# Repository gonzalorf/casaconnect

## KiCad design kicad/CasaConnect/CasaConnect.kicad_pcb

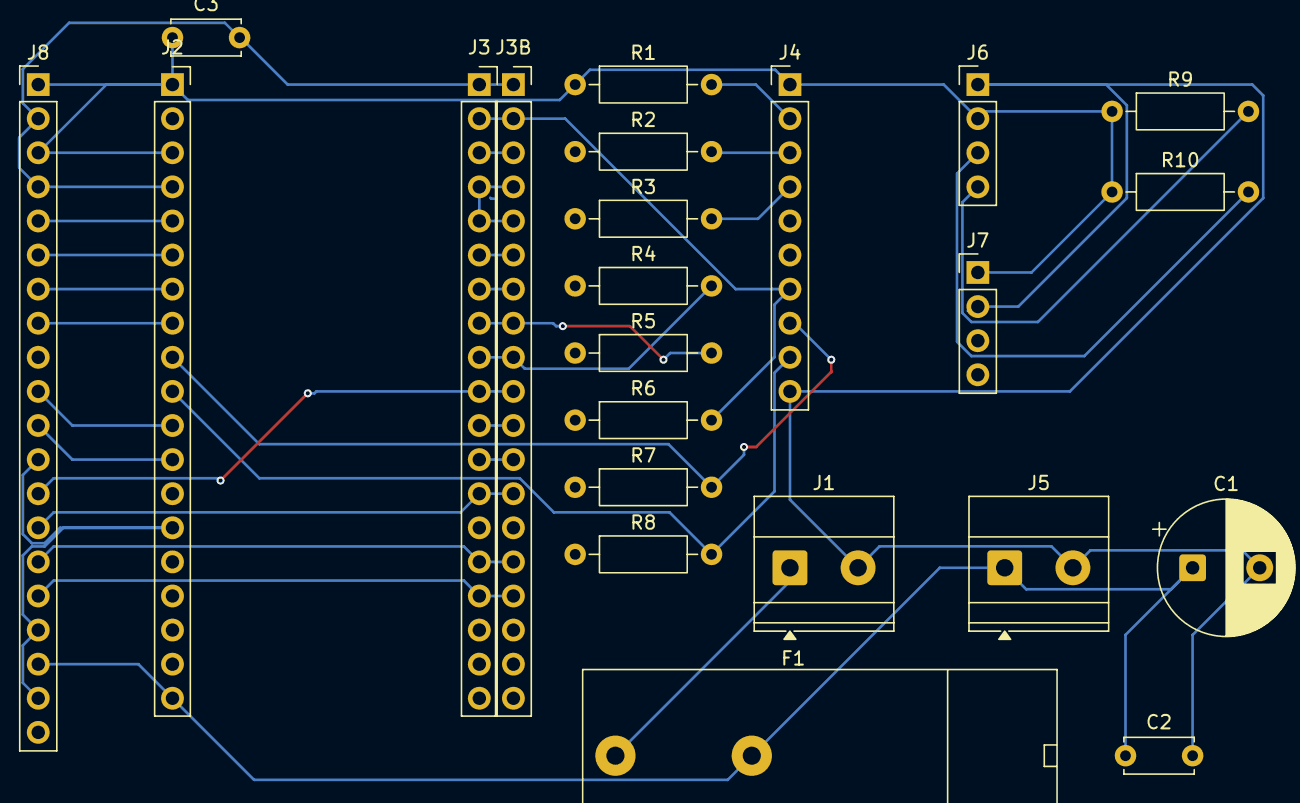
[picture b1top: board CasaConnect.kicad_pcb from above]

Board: 2 copper layers, 23 parts (0 on the bottom side), 26 nets.

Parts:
C1: 1000uF 16V; CP_Radial_D10.0mm_P5.00mm
C2, C3: 100nF; C_Disc_D5.0mm_W2.5mm_P5.00mm
F1: 2A; Fuseholder_Cylinder-5x20mm_Bulgin_FX0457_Horizontal_Closed
J1, J5: bornera 2 vias; TerminalBlock_Phoenix_MKDS-1,5-2-5.08_1x02_P5.08mm_Horizont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
J2, J3, J3B: header hembra 1x19; PinSocket_1x19_P2.54mm_Vertical
J4: header macho 1x10; PinHeader_1x10_P2.54mm_Vertical
J6, J7: header macho 1x4; PinHeader_1x04_P2.54mm_Vertical
J8: header macho 1x20; PinHeader_1x20_P2.54mm_Vertical
R1, R2, R3, R4, R5, R6, R7, R8: 10k; R_Axial_DIN0207_L6.3mm_D2.5mm_P10.16mm_Horizontal
R9, R10: 4.7k; R_Axial_DIN0207_L6.3mm_D2.5mm_P10.16mm_Horizontal

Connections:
+3V3: C3.1, J2.1, J4.1, J6.2, J7.1, J8.1, R1.1, R2.1, R3.1, R4.1, R5.1, R6.1, R7.1, R8.1, R9.1, R10.1
+5V: C1.1, C2.1, F1.2, J2.19, J5.1, J8.18
+5V_IN: F1.1, J1.1
GND: C1.2, C2.2, C3.2, J1.2, J2.14, J3.1, J3.7, J3B.1, J3B.7, J4.10, J5.2, J6.1, J7.2, J8.2, J8.9, J8.12, J8.17, J8.19
IN_2: J3.15, J3B.15, J8.15
IN_4: J3.13, J3B.13, J8.14
IN_5: J3.10, J3B.10, J8.13
IN_14: J2.12, J8.11
IN_15: J3.16, J3B.16, J8.16
IN_27: J2.11, J8.10
IN_32: J2.7, J8.7
IN_33: J2.8, J8.8
IN_34: J2.5, J8.5
IN_35: J2.6, J8.6
IN_36: J2.3, J8.3
IN_39: J2.4, J8.4
RLY1: J2.15, J4.2, R1.2
RLY2: J3.12, J3B.12, J4.3, R2.2
RLY3: J3.11, J3B.11, J4.4, R3.2
RLY4: J3.9, J3B.9, J4.5, R4.2
RLY5: J3.8, J3B.8, J4.6, R5.2
RLY6: J3.2, J3B.2, J4.7, R6.2
RLY7: J2.9, J4.8, R7.2
RLY8: J2.10, J4.9, R8.2
SCL: J3.3, J3B.3, J6.3, J7.4, R10.2
SDA: J3.6, J3B.6, J6.4, J7.3, R9.2

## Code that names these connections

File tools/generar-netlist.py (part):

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    net_limpio(35),    # 6  GPIO35
    net_limpio(32),    # 7  GPIO32
    net_limpio(33),    # 8  GPIO33
    "RLY7",            # 9  GPIO25
    "RLY8",            # 10 GPIO26
    net_limpio(27),    # 11 GPIO27
    net_limpio(14),    # 12 GPIO14
    "NC",              # 13 GPIO12  <-- strapping critico, NO USAR
    "GND",             # 14 GND
    "RLY1",            # 15 GPIO13
    "NC",              # 16 SD2
    "NC",              # 17 SD3
    "NC",              # 18 CMD
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
SOCKET_DER = [
    "GND",             # 1  GND
    "RLY6",            # 2  GPIO23
    "SCL",             # 3  GPIO22
    "NC",              # 4  TXD (GPIO1) - UART0, reservado
    "NC",              # 5  RXD (GPIO3) - UART0, reservado
    "SDA",             # 6  GPIO21
    "GND",             # 7  GND
    "RLY5",            # 8  GPIO19
    "RLY4",            # 9  GPIO18
    net_limpio(5),     # 10 GPIO5
    "RLY3",            # 11 GPIO17
    "RLY2",            # 12 GPIO16
    net_limpio(4),     # 13 GPIO4
    "NC",              # 14 GPIO0  <-- boton BOOT
    net_limpio(2),     # 15 GPIO2
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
